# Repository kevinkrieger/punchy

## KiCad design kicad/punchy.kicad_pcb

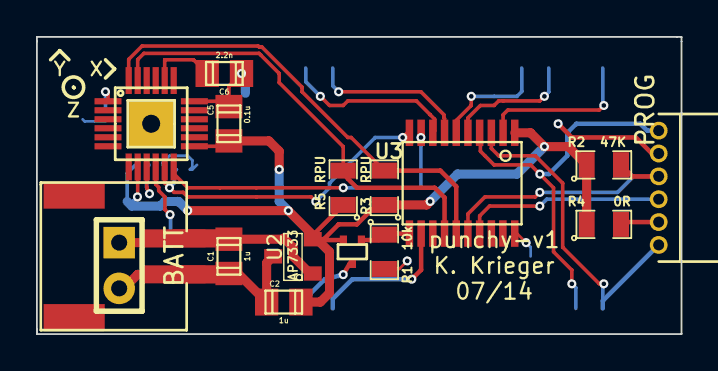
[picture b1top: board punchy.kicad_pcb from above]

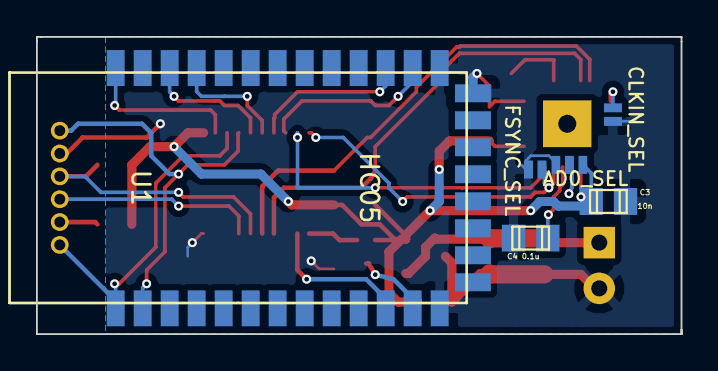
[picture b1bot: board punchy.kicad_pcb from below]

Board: 2 copper layers, 35.8 x 16.5 mm, 22 parts (6 on the bottom side), 24 nets.

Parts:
BT1: BATTERY; HEADER-2x0.1inch
C1, C2: 1u; c_0805
C3: 10n; c_0805
C4, C5: 0.1u; c_0805
C6: 2.2n; c_0805
J1: PROG; 851-87-20-006-001101
JP1: AD0_SEL; SOLDER_JUMPER_3
JP2: CLKIN_SEL; SOLDER_JUMPER
JP3: FSYNC_SEL; SOLDER_JUMPER
P1: BATT; S2B-PH-SM4-TB
Q1: DMG1012T-7; SOT523
R1: 10k; SM0805
R2: 47K; SM0805
R3, R5: RPU; SM0805
R4: 0R; SM0805
U1: HC05
U2: AP7333; SOT23
U3: MSP430G2X53; tssop-20
U4: MPU6050; qfn24_hand_solderable

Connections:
+BATT: BT1.1, C1.1, P1.2, U2.1
/BT_BLUE: U1.31, U3.6
/BT_DISCONNECT: U1.23, U3.8
/BT_KEY: U1.34, U3.2
/BT_ON: Q1.G, R1.1, U3.11
/BT_RED: U1.32, U3.5
/BT_RESET: U1.11, U3.12
/BT_RX: J1.6, U1.2, U3.4
/BT_STATUS: U1.24, U3.7
/BT_TX: J1.1, U1.1, U3.3
/CLKIN: JP2.2, U4.1
/FSYNC: JP3.2, U3.10, U4.11
/INT: U3.9, U4.12
/SCL: R5.2, U3.14, U4.23
/SDA: R3.2, U3.15, U4.24
GND: BT1.2, C1.2, C2.2, C3.2, C4.2, C5.2, C6.2, J1.5, JP1.1, JP2.1, JP3.1, P1.1, R1.2, U1.13, U1.21, U1.22, U2.3, U3.20, U4.18
unnamed: Q1.D, U1.12
unnamed: J1.3, U3.17
unnamed: J1.4, R2.2, U3.16
unnamed: J1.2, R4.2
unnamed: C4.1, U4.10
unnamed: JP1.2, U4.9
unnamed: C6.1, U4.20
VCC: C2.1, C3.1, C5.1, JP1.3, Q1.S, R2.1, R3.1, R4.1, R5.1, U2.2, U3.1, U4.8, U4.13

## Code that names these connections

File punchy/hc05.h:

#ifndef HC05_H
#define HC05_H
#include <legacymsp430.h>
#include <stdint.h>
#include <msp430g2553.h>
#include "utility.h"

#define BT_KEY          BIT0    // Port 1
#define BT_RED          BIT3    // Port 1
#define BT_BLUE         BIT4    // Port 1
#define BT_STATUS       BIT5    // Port 1
#define BT_DISCONNECT   BIT0    // Port 2
#define BT_RESET        BIT4    // Port 2
#define BT_ON 		    BIT3    // Port 2
#define BAUD		    9600
#define BT_RX 		    BIT1	// Which pin on port 2 is the RX pin?
#define BT_TX 		    BIT2	// Which pin on port 2 is the TX pin?
#define CYCLES_PER_US (FOSC/1000000)
#define __delay_us(delay) __delay_cycles((CYCLES_PER_US*delay))
#define __baud_to_uca0br(baud) (FOSC/(baud))

uint8_t TXData;
uint8_t hc05_buffer[32];

void hc05_transmit(char *data, uint16_t transmit_length);

void hc05_init(uint16_t uca0br);

void hc05_off();

void hc05_on();

void hc05_setspeed(uint32_t speed);

static inline void sendAck() {
	hc05_transmit("A",1);
}


#endif

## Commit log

2014-08-17 Ignoring more files
2014-08-17 Sort of working version of punchy.
2014-08-18 Added code to respond to UART commands. Wakeup, sleep, reset, accel, gyro, temp... seems to work well enough
2014-08-18 Added data from logic analyzer
2014-08-18 refactored i2c library
2014-08-18 refactored hc05 uart library
2014-08-18 refactored mpu6050 routines
2014-08-18 refactored all. Removed unecessary comments and cleaned up
2014-08-18 finished adding board level defines to bt lib
2014-08-18 Fixed formatting
2014-08-18 Added defines
2014-08-18 Added sprintf to send accel, gyro and temp properly in human readable format over hc05
2014-08-20 Fixed i2c library... now works with mpu6050 dmp init
2014-08-20 Working code that produces interrupts periodically from DMP
2014-08-20 Added data dumps
2014-08-20 Added data dump from first working dmp init
2014-08-20 Added debug #ifdefs for print statements. Much less memory is used now. Fixed location of tempbuf definition so main() can use it
2014-08-20 Working version, but any more memory use causes unpredictable failures. Need to trim the fat before I can write any actual application code
2014-08-25 Added on code, off code, set speed code and fixed port pin inits so they don't have unintended effects. For hc05 lib.
2014-08-25 Added working teapot code. Have working motion code as well. Needs tweaking, perhaps with duration.
2014-08-25 added comments for clock rate divider
2014-08-25 Added data dump for dmp, added text to schematic explaining why DMG1012t-7 will not work in its configuration. Can be fixed by flipping source and drain or using p-channel fet
2014-08-25 Changed dmp init code to 50Hz, moved around debug #ifdefs
2014-08-25 Modified teapot code for my liking
2014-08-25 Comment updated
2014-08-26 Fixed board with pnp, now hc05 BT_ON is active low
2014-08-26 Change the motion detect duration. Lowered to 40ms seems good for punch detection
2014-08-27 Convenience function to calculate uca0br bytes given a baud rate - uses FOSC
2014-08-27 Calculating ucb0br value using FOSC. Currently set to 400kHz, max, and working.
2014-08-27 Added state flags for dmp mode or motion detect mode. Fixed motion detect mode enable code(added interrupt setup for p2). Set to calibrated 16MHz - tested and working. I can get motion detect only in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
2014-08-27 Increased delay due to increasing FOSC. This should be max required.
2014-08-28 Fixed HC05 intialization to change baud. Added utility delay_ms function. Updated I2c init to use FOSC and define for I2C speed.
2014-08-28 Added data captures with blueterm that show several motion captures where I sort of punch the air with the device in hand
2014-08-28 Bug fix - need to wait until last byte is finished transmitting or we can't be sure it will make it out the serial port properly (depends upon what happens to uart clock when function returns!
2014-08-28 cleaned up comments, added motion detect for 200 samples, changed accel to +/- 16g.
2014-12-16 Added picture for one punch and some data. Modified to have motion detection faster (35ms vs 80ms)
2014-12-16 Removed unecessary and old commented code
2017-02-04 Added in estimate for # of memory bytes allocated
2017-02-04 Added licence header
